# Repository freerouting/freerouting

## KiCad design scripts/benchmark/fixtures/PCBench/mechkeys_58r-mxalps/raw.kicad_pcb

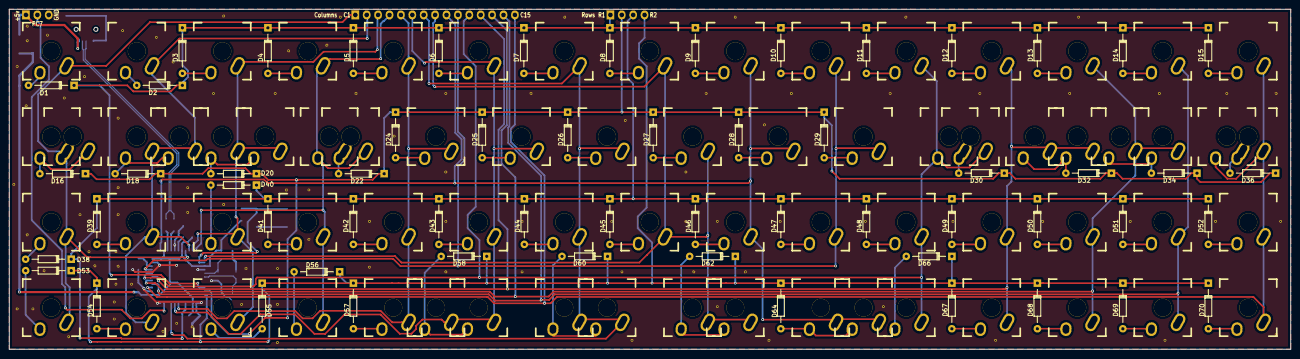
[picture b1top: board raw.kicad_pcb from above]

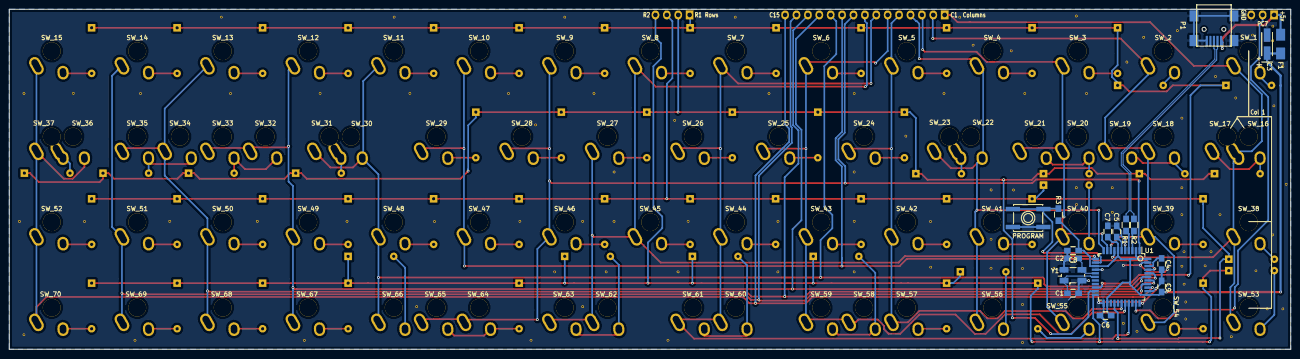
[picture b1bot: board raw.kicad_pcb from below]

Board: 2 copper layers, 285.5 x 75.8 mm, 148 parts (17 on the bottom side), 90 nets.

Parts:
C1, C2, C4, C6, C7, C8, C9: C_Small; C_0805_HandSoldering
C3: CP_Small; TantalC_SizeA_EIA-3216_HandSoldering
C5: 1µF; C_0805_HandSoldering
D1, D2, D3, D4, D5, D6, D7, D8, D9, D10, D11, D12, D13, D14, D15, D16, D18, D20, D22, D24, D25, D26, D27, D28, D29, D30, D32, D34, D36, D38, D39, D40, D41, D42, D43, D44, D45, D46, D47, D48, D49, D50, D51, D52, D53, D54, D55, D56, D57, D58, D60, D62, D64, D66, D67, D68, D69, D70: D; Diode_DO-35_SOD27_Horizontal_RM10
F1: F_Small; Fuse_SMD1206_HandSoldering
P1: USB_OTG; USB_Mini-B
P2: CONN_01X03; Socket_Strip_Straight_1x03_NoOverlay
P3: CONN_01X15; Socket_Strip_Straight_1x15_NoOverlay
P4: CONN_01X04; Socket_Strip_Straight_1x04_NoOverlay
PROGRAM: SW_PUSH; SW_SPST_EVQP0
R1, R2: 22; R_0805_HandSoldering
R3: 10k; R_0805_HandSoldering
SW_1, SW_2, SW_3, SW_4, SW_5, SW_6, SW_7, SW_8, SW_9, SW_10, SW_11, SW_12, SW_13, SW_14, SW_15, SW_16, SW_17, SW_18, SW_19, SW_20, SW_21, SW_22, SW_23, SW_24, SW_25, SW_26, SW_27, SW_28, SW_29, SW_30, SW_31, SW_32, SW_33, SW_34, SW_35, SW_36, SW_37, SW_38, SW_39, SW_40, SW_41, SW_42, SW_43, SW_44, SW_45, SW_46, SW_47, SW_48, SW_49, SW_50, SW_51, SW_52, SW_53, SW_54, SW_55, SW_56, SW_57, SW_58, SW_59, SW_60, SW_61, SW_62, SW_63, SW_64, SW_65, SW_66, SW_67, SW_68, SW_69, SW_70: MX_LED; MXALPS-NOLED
U1: ATmega32U4; LQFP-44_10x10mm_Pitch0.8mm
Y1: Crystal_Small; Crystal_SMD_5032_4Pads

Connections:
+5V: C3.1, C6.1, C7.1, C8.1, C9.1, F1.2, R3.2, U1.2, U1.7, U1.14, U1.24, U1.34, U1.44
C1: P3.1, SW_1.SW1, SW_16.SW1, SW_17.SW2, SW_38.SW1, SW_53.SW1, U1.8
C2: P3.2, SW_2.SW1, SW_18.SW1, SW_19.SW1, SW_39.SW1, SW_54.SW1, U1.9
C3: P3.3, SW_3.SW1, SW_20.SW1, SW_21.SW1, SW_40.SW1, SW_55.SW1, U1.10
C4: P3.4, SW_4.SW1, SW_22.SW2, SW_23.SW1, SW_41.SW1, SW_56.SW1, U1.11
C5: P3.5, SW_5.SW1, SW_24.SW1, SW_42.SW1, SW_57.SW1, U1.28
C6: P3.6, SW_6.SW1, SW_25.SW1, SW_43.SW1, SW_58.SW1, SW_59.SW1, U1.29
C7: P3.7, SW_7.SW1, SW_26.SW1, SW_44.SW1, SW_60.SW1, SW_61.SW1, U1.30
C8: P3.8, SW_8.SW1, SW_27.SW1, SW_45.SW1, SW_62.SW1, SW_63.SW1, U1.12
C9: P3.9, SW_9.SW1, SW_28.SW1, SW_46.SW1, SW_64.SW1, SW_65.SW1, U1.1
C10: P3.10, SW_10.SW1, SW_29.SW1, SW_47.SW1, U1.41
C11: P3.11, SW_11.SW1, SW_30.SW2, SW_31.SW1, SW_48.SW1, SW_66.SW1, U1.40
C12: P3.12, SW_12.SW1, SW_32.SW1, SW_33.SW1, SW_49.SW1, SW_67.SW1, U1.39
C13: P3.13, SW_13.SW1, SW_34.SW1, SW_35.SW1, SW_50.SW1, SW_68.SW1, U1.38
C14: P3.14, SW_14.SW1, SW_51.SW1, SW_69.SW1, U1.37
C15: P3.15, SW_15.SW1, SW_36.SW2, SW_37.SW1, SW_52.SW1, SW_70.SW1, U1.36
D+: R1.1, U1.4
D-: R2.1, U1.3
GND: C1.1, C2.2, C3.2, C4.2, C5.2, C6.2, C7.2, C8.2, C9.2, P1.5, P1.6, P2.3, PROGRAM.1, U1.5, U1.15, U1.23, U1.33, U1.35, U1.43, Y1.3
unnamed: C1.2, U1.17, Y1.1
unnamed: C2.1, U1.16, Y1.2
unnamed: C4.1, U1.42
unnamed: C5.1, U1.6
unnamed: D1.2, SW_1.SW2
unnamed: D2.2, SW_2.SW2
unnamed: D3.2, SW_3.SW2
unnamed: D4.2, SW_4.SW2
unnamed: D5.2, SW_5.SW2
unnamed: D6.2, SW_6.SW2
unnamed: D7.2, SW_7.SW2
unnamed: D8.2, SW_8.SW2
unnamed: D9.2, SW_9.SW2
unnamed: D10.2, SW_10.SW2
unnamed: D11.2, SW_11.SW2
unnamed: D12.2, SW_12.SW2
unnamed: D13.2, SW_13.SW2
unnamed: D14.2, SW_14.SW2
unnamed: D15.2, SW_15.SW2
unnamed: D16.2, SW_16.SW2, SW_17.SW1
unnamed: D18.2, SW_18.SW2, SW_19.SW2
unnamed: D20.2, SW_20.SW2, SW_21.SW2
unnamed: D22.2, SW_22.SW1, SW_23.SW2
unnamed: D24.2, SW_24.SW2
unnamed: D25.2, SW_25.SW2
unnamed: D26.2, SW_26.SW2
unnamed: D27.2, SW_27.SW2
unnamed: D28.2, SW_28.SW2
unnamed: D29.2, SW_29.SW2
unnamed: D30.2, SW_30.SW1, SW_31.SW2
unnamed: D32.2, SW_32.SW2, SW_33.SW2
unnamed: D34.2, SW_34.SW2, SW_35.SW2
unnamed: D36.2, SW_36.SW1, SW_37.SW2
unnamed: D38.2, SW_38.SW2
unnamed: D39.2, SW_39.SW2
unnamed: D40.2, SW_40.SW2
unnamed: D41.2, SW_41.SW2
unnamed: D42.2, SW_42.SW2
unnamed: D43.2, SW_43.SW2
unnamed: D44.2, SW_44.SW2
unnamed: D45.2, SW_45.SW2
unnamed: D46.2, SW_46.SW2
unnamed: D47.2, SW_47.SW2
unnamed: D48.2, SW_48.SW2
unnamed: D49.2, SW_49.SW2
unnamed: D50.2, SW_50.SW2
unnamed: D51.2, SW_51.SW2
unnamed: D52.2, SW_52.SW2
unnamed: D53.2, SW_53.SW2
unnamed: D54.2, SW_54.SW2
unnamed: D55.2, SW_55.SW2
unnamed: D56.2, SW_56.SW2
unnamed: D57.2, SW_57.SW2
unnamed: D58.2, SW_58.SW2, SW_59.SW2
unnamed: D60.2, SW_60.SW2, SW_61.SW2
unnamed: D62.2, SW_62.SW2, SW_63.SW2
unnamed: D64.2, SW_64.SW2, SW_65.SW2
unnamed: D66.2, SW_66.SW2
unnamed: D67.2, SW_67.SW2
unnamed: D68.2, SW_68.SW2
unnamed: D69.2, SW_69.SW2
unnamed: D70.2, SW_70.SW2
unnamed: PROGRAM.2, R3.1, U1.13
PC7: P2.2, U1.32
R1: D1.1, D2.1, D3.1, D4.1, D5.1, D6.1, D7.1, D8.1, D9.1, D10.1, D11.1, D12.1, D13.1, D14.1, D15.1, P4.1, U1.20
R2: D16.1, D18.1, D20.1, D22.1, D24.1, D25.1, D26.1, D27.1, D28.1, D29.1, D30.1, D32.1, D34.1, D36.1, P4.2, U1.21
R3: D38.1, D39.1, D40.1, D41.1, D42.1, D43.1, D44.1, D45.1, D46.1, D47.1, D48.1, D49.1, D50.1, D51.1, D52.1, P4.3, U1.26
R4: D53.1, D54.1, D55.1, D56.1, D57.1, D58.1, D60.1, D62.1, D64.1, D66.1, D67.1, D68.1, D69.1, D70.1, P4.4, U1.22
USB+: P1.3, R1.2
USB-: P1.2, R2.2
VUSB: F1.1, P1.1, P2.1

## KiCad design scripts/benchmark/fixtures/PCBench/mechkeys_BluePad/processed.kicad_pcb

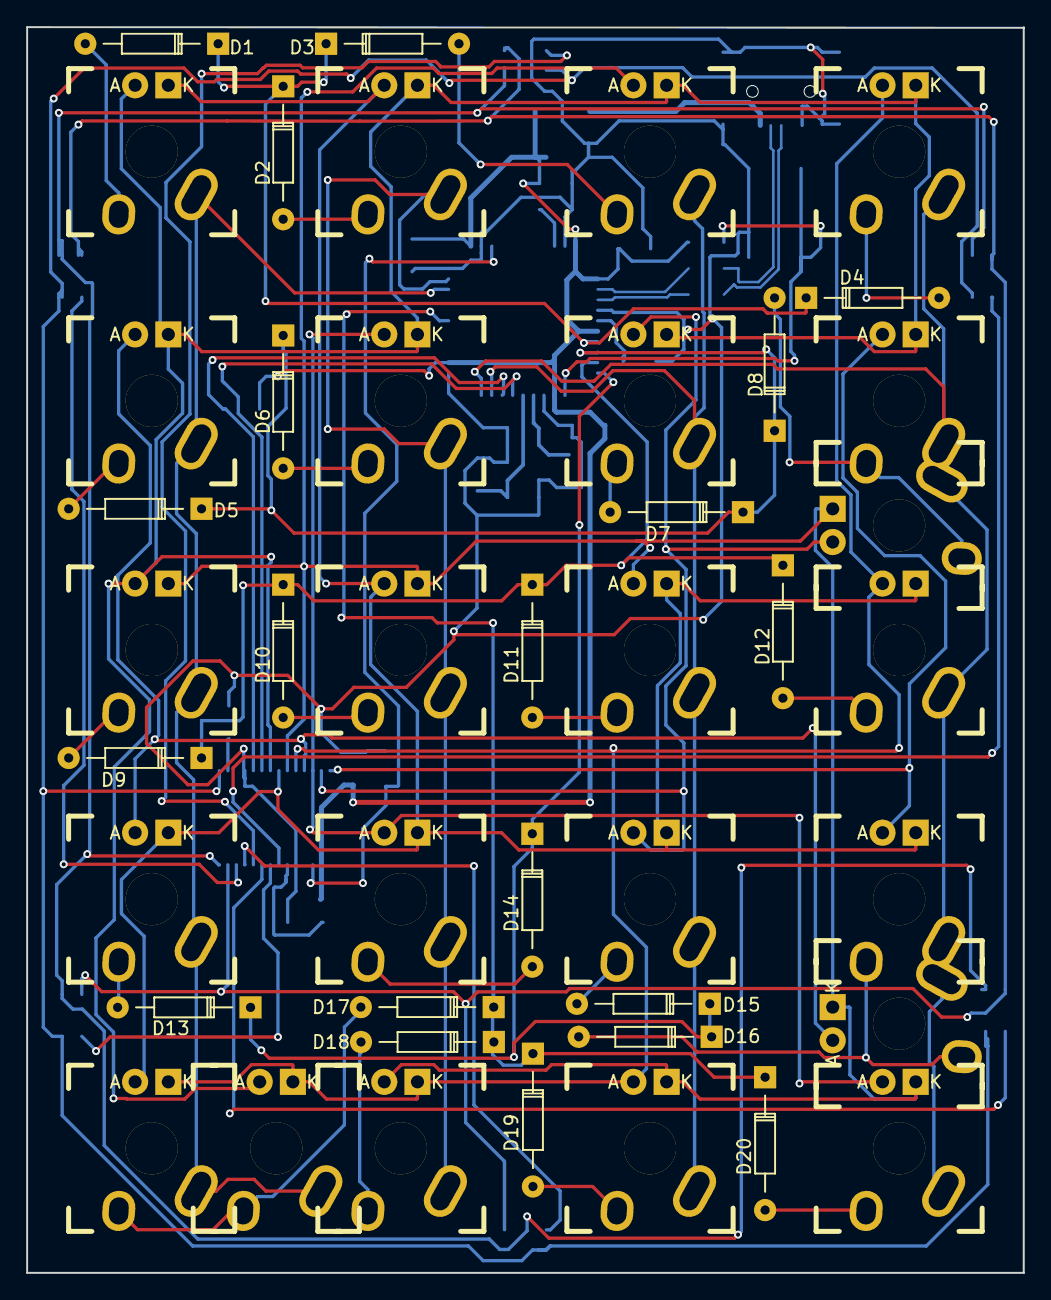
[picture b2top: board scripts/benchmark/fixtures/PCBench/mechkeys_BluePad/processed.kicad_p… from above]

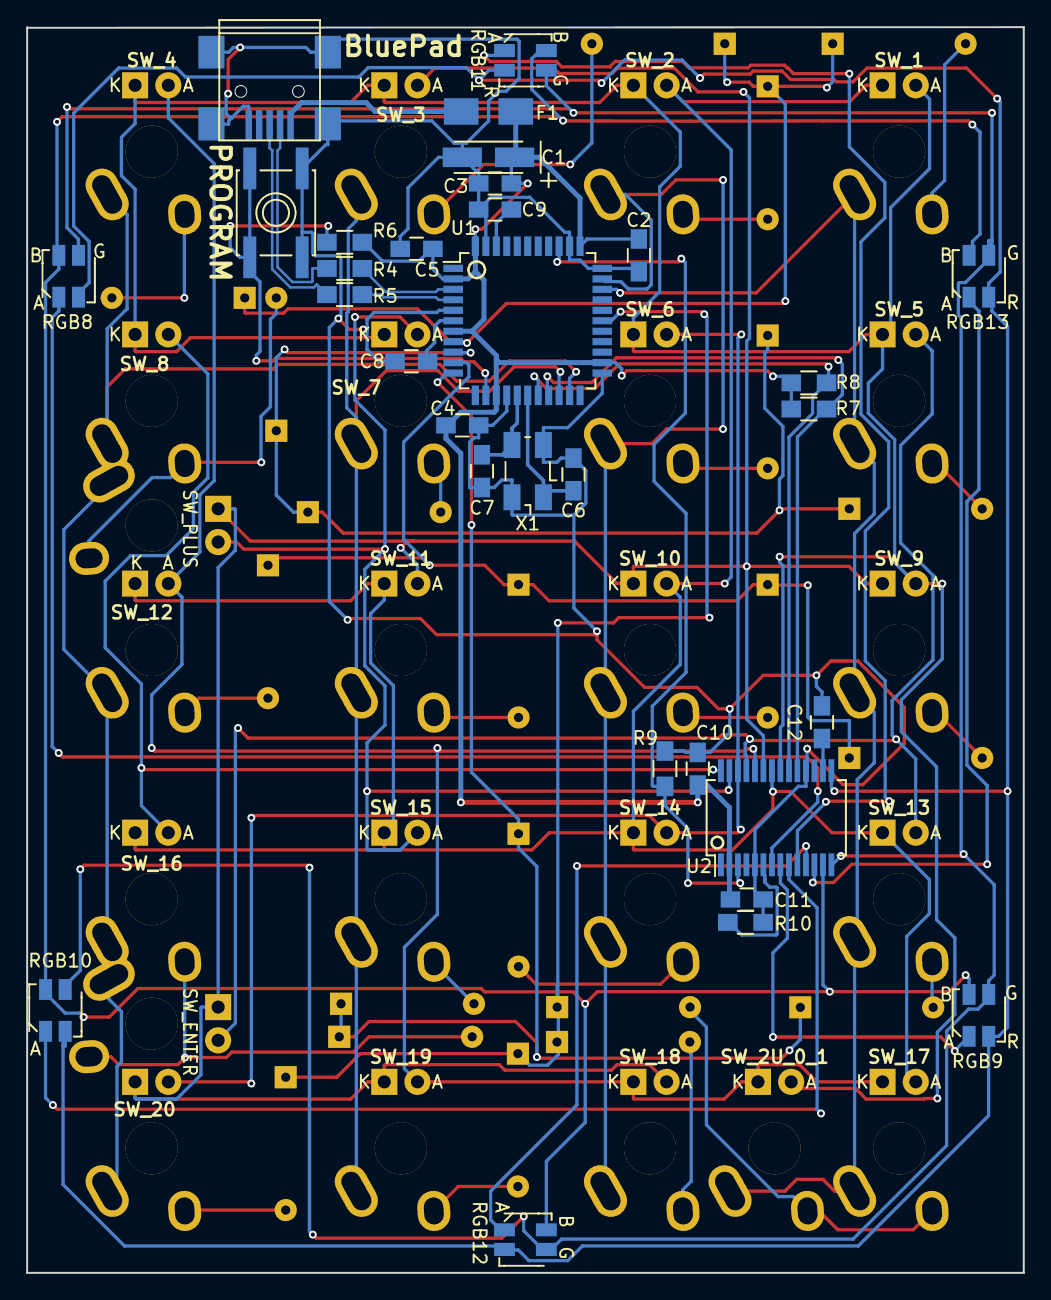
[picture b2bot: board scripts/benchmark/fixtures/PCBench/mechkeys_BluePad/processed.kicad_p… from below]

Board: 2 copper layers, 76.2 x 95.2 mm, 74 parts (31 on the bottom side), 63 nets.

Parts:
C1: 10µF; TantalC_SizeA_EIA-3216_HandSoldering
C2, C3, C4, C5, C9, C11, C12: 0.1µF; C_0805_HandSoldering
C6, C7: 18pF; C_0805_HandSoldering
C8, C10: 1µF; C_0805_HandSoldering
D1, D2, D3, D4, D5, D6, D7, D8, D9, D10, D11, D12, D13, D14, D15, D16, D17, D18, D19, D20: D; Diode_DO-35_SOD27_Horizontal_RM10
F1: FP_Small; Fuse_SMD1206_HandSoldering
J1: USB_OTG; USB_Mini-B
R4, R5: 22; R_0805_HandSoldering
R6: 10k; R_0805_HandSoldering
R7, R8: 4.7KΩ; R_0805_HandSoldering
R9: 100KΩ; R_0805_HandSoldering
R10: 20KΩ; R_0805_HandSoldering
RGB8, RGB9, RGB10, RGB11, RGB12, RGB13: Led_RGB_CA; SMP4-RGB
SW1: SW_RST; SW_SPST_EVQP0
SW_1, SW_2, SW_2U_0_1, SW_2U_PLUS_1, SW_3, SW_4, SW_5, SW_6, SW_7, SW_8, SW_9, SW_10, SW_11, SW_12, SW_13, SW_14, SW_15, SW_16, SW_17, SW_18, SW_19, SW_20: MX_LED; MXALPS
SW_2U_ENTER_1: MX_LED; MXALPS_LED_PANEL
U1: ATMEGA32U4RC-A; TQFP-44_10x10mm_Pitch0.8mm
U2: IS31FL3731; SSOP-28_5.3x10.2mm_Pitch0.65mm
X1: 16Mhz; Crystal_SMD_5032_4Pads

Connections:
+5V: C1.1, C2.1, C3.1, C4.1, C5.1, C10.1, C11.1, F1.2, R6.2, R7.1, R8.1, U1.2, U1.7, U1.14, U1.24, U1.34, U1.44, U2.2
C1: SW_1.SW1, SW_2U_0_1.SW1, SW_5.SW1, SW_9.SW1, SW_13.SW1, SW_17.SW1, U1.31
C2: SW_2.SW1, SW_6.SW1, SW_10.SW1, SW_14.SW1, SW_18.SW1, U1.32
C3: SW_3.SW1, SW_7.SW1, SW_11.SW1, SW_15.SW1, SW_19.SW1, U1.20
C4: SW_2U_ENTER_1.SW1, SW_2U_PLUS_1.SW1, SW_4.SW1, SW_8.SW1, SW_12.SW1, SW_16.SW1, SW_20.SW1, U1.21
CA1: SW_1.A, SW_2.K, SW_2U_0_1.A, SW_3.K, SW_4.K, SW_5.K, SW_6.K, SW_7.K, SW_8.K, SW_9.A, U2.21
CA2: SW_1.K, SW_2.A, SW_10.A, SW_11.K, SW_12.K, SW_13.K, SW_14.K, SW_15.K, SW_16.K, SW_17.A, U2.22
CA3: SW_2U_ENTER_1.K, SW_2U_PLUS_1.K, SW_3.A, SW_9.K, SW_10.K, SW_11.A, SW_18.A, SW_19.K, SW_20.K, U2.23
CA4: SW_2U_0_1.K, SW_4.A, SW_12.A, SW_17.K, SW_18.K, SW_19.A, U2.24
CA5: SW_2U_ENTER_1.A, SW_5.A, SW_13.A, U2.25
CA6: SW_6.A, SW_14.A, SW_20.A, U2.26
CA7: SW_2U_PLUS_1.A, SW_7.A, SW_15.A, U2.27
CA8: SW_8.A, SW_16.A, U2.28
CB1: RGB8.1, U2.7
CB2: RGB9.1, U2.8
CB3: RGB10.1, U2.9
CB4: RGB11.1, U2.10
CB5: RGB12.1, U2.11
CB6: RGB13.1, U2.12
CB7: RGB8.4, RGB9.4, RGB10.4, RGB11.4, RGB12.4, RGB13.4, U2.13
CB8: RGB8.3, RGB9.3, RGB10.3, RGB11.3, RGB12.3, RGB13.3, U2.14
CB9: RGB8.2, RGB9.2, RGB10.2, RGB11.2, RGB12.2, RGB13.2, U2.15
D+: R5.1, U1.4
D-: R4.1, U1.3
GND: C1.2, C2.2, C3.2, C4.2, C5.2, C6.2, C7.2, C8.2, C9.2, C10.2, C11.2, C12.2, J1.5, J1.6, R9.2, R10.2, SW1.1, U1.5, U1.15, U1.23, U1.33, U1.35, U1.43, U2.5, U2.18, X1.3
LED_NSRT: R9.1, U1.36, U2.3
LED_SCL: R8.2, U1.18, U2.20
LED_SDA: R7.2, U1.19, U2.19
unnamed: C6.1, U1.17, X1.1
unnamed: C7.1, U1.16, X1.2
unnamed: C8.1, U1.6
unnamed: C9.1, U1.42
unnamed: C12.1, U2.16
unnamed: D1.2, SW_1.SW2
unnamed: D2.2, SW_2.SW2
unnamed: D3.2, SW_3.SW2
unnamed: D4.2, SW_4.SW2
unnamed: D5.2, SW_5.SW2
unnamed: D6.2, SW_6.SW2
unnamed: D7.2, SW_7.SW2
unnamed: D8.2, SW_2U_PLUS_1.SW2, SW_8.SW2
unnamed: D9.2, SW_9.SW2
unnamed: D10.2, SW_10.SW2
unnamed: D11.2, SW_11.SW2
unnamed: D12.2, SW_12.SW2
unnamed: D13.2, SW_13.SW2
unnamed: D14.2, SW_14.SW2
unnamed: D15.2, SW_15.SW2
unnamed: D16.2, SW_2U_ENTER_1.SW2, SW_16.SW2
unnamed: D17.2, SW_2U_0_1.SW2, SW_17.SW2
unnamed: D18.2, SW_18.SW2
unnamed: D19.2, SW_19.SW2
unnamed: D20.2, SW_20.SW2
unnamed: F1.1, J1.1
unnamed: R10.1, U2.6
R1: D1.1, D2.1, D3.1, D4.1, U1.8
R2: D5.1, D6.1, D7.1, D8.1, U1.9
R3: D9.1, D10.1, D11.1, D12.1, U1.10
R4: D13.1, D14.1, D15.1, D16.1, U1.11
R5: D17.1, D18.1, D19.1, D20.1, U1.28
RST: R6.1, SW1.2, U1.13
USB+: J1.3, R5.2
USB-: J1.2, R4.2

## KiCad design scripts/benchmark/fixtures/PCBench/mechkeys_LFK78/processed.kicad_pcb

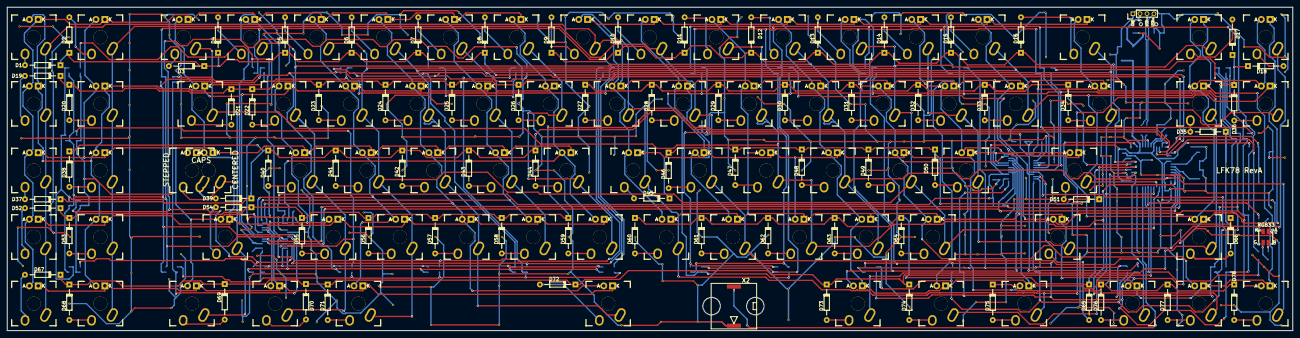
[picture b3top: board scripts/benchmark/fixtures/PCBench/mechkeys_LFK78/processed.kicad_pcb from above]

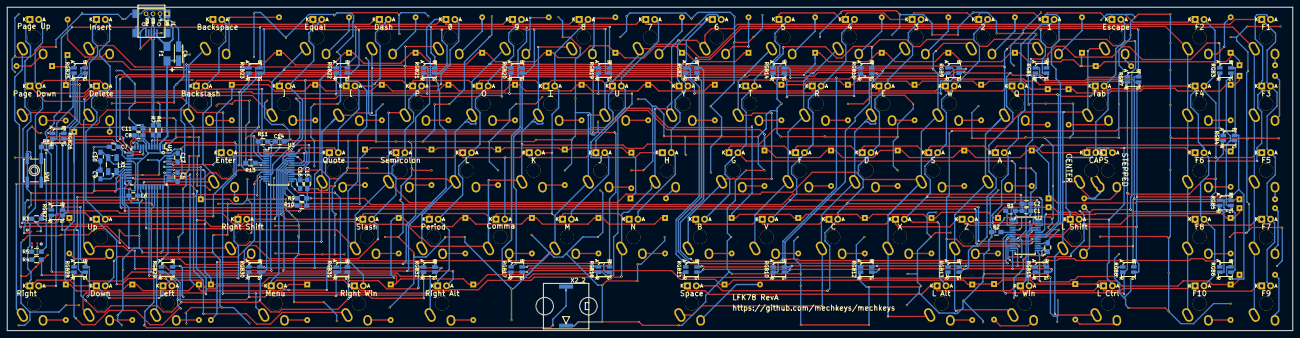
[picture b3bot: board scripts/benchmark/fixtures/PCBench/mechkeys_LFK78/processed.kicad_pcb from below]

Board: 2 copper layers, 367.8 x 92.5 mm, 226 parts (66 on the bottom side), 159 nets.

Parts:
C1, C11, C14: 1µF; C_0805_HandSoldering
C2, C3, C5, C6, C7, C8, C12, C15, C16: 0.1µF; C_0805_HandSoldering
C4: 10µF; TantalC_SizeA_EIA-3216_HandSoldering
C9, C10: 18pF; C_0805_HandSoldering
CHERRY: MX; CHERRY_PCB_625H_STABILIZER
D1, D2, D3, D4, D5, D6, D7, D8, D9, D10, D11, D12, D13, D14, D15, D16, D17, D18, D19, D20, D21, D22, D23, D24, D25, D26, D27, D28, D29, D30, D31, D32, D33, D34, D35, D36, D37, D38, D39, D40, D41, D42, D43, D44, D45, D46, D47, D48, D49, D50, D51, D52, D53, D54, D55, D56, D57, D58, D59, D60, D61, D62, D63, D64, D65, D66, D67, D68, D69, D70, D71, D72, D73, D74, D75, D76, D77, D78: D; Diode_DO-35_SOD27_Horizontal_RM10
F1: FP_Small; Fuse_SMD1206_HandSoldering
J1: USB_OTG; USB_Mini-B
R1, R11: 10KΩ; R_0805_HandSoldering
R2, R13: 20KΩ; R_0805_HandSoldering
R3: 150Ω; R_0805_HandSoldering
R4, R5: 120Ω; R_0805_HandSoldering
R6, R7: 22; R_0805_HandSoldering
R8: 10k; R_0805_HandSoldering
R9, R10: 4.7KΩ; R_0805_HandSoldering
RGB1, RGB2, RGB3, RGB4, RGB5, RGB6, RGB7, RGB8, RGB9, RGB10, RGB11, RGB12, RGB13, RGB14, RGB15, RGB16, RGB17, RGB18, RGB19, RGB20, RGB21, RGB22, RGB23, RGB25, RGB26, RGB27, RGB28, RGB29, RGB30, RGB31, RGB32: Led_RGB_CA; SMP4-RGB
RGB33: Led_RGB_CA; SMP4-RGB-PIPE
SW1: SW_RST; SW_SPST_EVQP0
SW_A_40: MX_LED; MXALPS_LED_PANEL
SW_Alt_71, SW_Alt_73: MX_LED; MXALPS_LED_PANEL
SW_B_59: MX_LED; MXALPS_LED_PANEL
SW_Backspace_16: MX_LED; MXALPS_LED_PANEL
SW_C_57: MX_LED; MXALPS_LED_PANEL
SW_CapStep_39: MX_LED; MXALPS_LED_PANEL
SW_Caps_39: MX_LED; MXALPS_LED_PANEL
SW_Ctrl_69: MX_LED; MXALPS_LED_PANEL
SW_D_42: MX_LED; MXALPS_LED_PANEL
SW_Del_35: MX_LED; MXALPS_LED_PANEL
SW_E_24: MX_LED; MXALPS_LED_PANEL
SW_Enter_51: MX_LED; MXALPS_LED_PANEL
SW_F1_1, SW_F2_2, SW_F3_19, SW_F4_20, SW_F5_37, SW_F6_38, SW_F7_52, SW_F8_53, SW_F9_67, SW_F10_68: MX_LED; MXALPS_LED_PANEL
SW_F_43: MX_LED; MXALPS_LED_PANEL
SW_G_44: MX_LED; MXALPS_LED_PANEL
SW_H_45: MX_LED; MXALPS_LED_PANEL
SW_I_29: MX_LED; MXALPS_LED_PANEL
SW_Ins_17: MX_LED; MXALPS_LED_PANEL
SW_J_46: MX_LED; MXALPS_LED_PANEL
SW_K_47: MX_LED; MXALPS_LED_PANEL
SW_L_48: MX_LED; MXALPS_LED_PANEL
SW_M_61: MX_LED; MXALPS_LED_PANEL
SW_Menu_75: MX_LED; MXALPS_LED_PANEL
SW_N_60: MX_LED; MXALPS_LED_PANEL
SW_O_30: MX_LED; MXALPS_LED_PANEL
SW_P_31: MX_LED; MXALPS_LED_PANEL
SW_PgDn_36: MX_LED; MXALPS_LED_PANEL
SW_PgUp_18: MX_LED; MXALPS_LED_PANEL
SW_Q_22: MX_LED; MXALPS_LED_PANEL
SW_R_25: MX_LED; MXALPS_LED_PANEL
SW_S_41: MX_LED; MXALPS_LED_PANEL
SW_Shift_54, SW_Shift_65: MX_LED; MXALPS_LED_PANEL
SW_T_26: MX_LED; MXALPS_LED_PANEL
SW_Tab_21: MX_LED; MXALPS_LED_PANEL
SW_U_28: MX_LED; MXALPS_LED_PANEL
SW_V_58: MX_LED; MXALPS_LED_PANEL
SW_W_23: MX_LED; MXALPS_LED_PANEL
SW_Win_70, SW_Win_74: MX_LED; MXALPS_LED_PANEL
SW_X4Y1_3, SW_X5Y1_4, SW_X6Y1_5, SW_X7Y1_6, SW_X8Y1_7, SW_X8Y5_72, SW_X9Y1_8, SW_X10Y1_9, SW_X11Y1_10, SW_X12Y1_11, SW_X13Y1_12, SW_X13Y4_62, SW_X14Y1_13, SW_X14Y4_63, SW_X15Y1_14, SW_X15Y2_32, SW_X15Y3_49, SW_X15Y4_64, SW_X16Y1_15, SW_X16Y2_33, SW_X16Y3_50, SW_X17Y2_34, SW_X18Y5_76, SW_X19Y4_66, SW_X19Y5_77, SW_X20Y5_78: MX_LED; MXALPS_LED_PANEL
SW_X_56: MX_LED; MXALPS_LED_PANEL
SW_Y_27: MX_LED; MXALPS_LED_PANEL
SW_Z_55: MX_LED; MXALPS_LED_PANEL
U1: ATMEGA32U4RC-A; TQFP-44_10x10mm_Pitch0.8mm
U2, U3: IS31FL3731; SSOP-28_5.3x10.2mm_Pitch0.65mm
X1: 16Mhz; Crystal_SMD_5032_4Pads
X2, X2_2: PiezoelectricCrystal-TwoElectrodes_EN60617_04-07-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; piezo-12x12

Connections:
+5V: C1.1, C2.1, C4.1, C5.1, C6.1, C7.1, C8.1, C14.1, C15.1, F1.2, R1.2, R8.2, R9.1, R10.1, R11.2, RGB33.1, U1.2, U1.7, U1.14, U1.24, U1.34, U1.44, U2.2, U3.2, U3.18
AUDIO: U1.31, X2.2, X2_2.2
C1: SW_F1_1.SW1, SW_F3_19.SW1, SW_F5_37.SW1, SW_F7_52.SW1, SW_F9_67.SW1, SW_H_45.SW1, SW_Menu_75.SW1, SW_N_60.SW1, SW_X10Y1_9.SW1, SW_Y_27.SW1, U1.1
C2: SW_F2_2.SW1, SW_F4_20.SW1, SW_F6_38.SW1, SW_F8_53.SW1, SW_F10_68.SW1, SW_J_46.SW1, SW_M_61.SW1, SW_U_28.SW1, SW_X11Y1_10.SW1, SW_X18Y5_76.SW1, U1.36
C3: SW_CapStep_39.SW2, SW_Caps_39.SW1, SW_Ctrl_69.SW1, SW_I_29.SW1, SW_K_47.SW1, SW_Shift_54.SW1, SW_Tab_21.SW1, SW_X4Y1_3.SW1, SW_X12Y1_11.SW1, SW_X13Y4_62.SW1, SW_X19Y5_77.SW1, U1.20
C4: SW_A_40.SW1, SW_L_48.SW1, SW_O_30.SW1, SW_Q_22.SW1, SW_Win_70.SW1, SW_X5Y1_4.SW1, SW_X13Y1_12.SW1, SW_X14Y4_63.SW1, SW_X20Y5_78.SW1, SW_Z_55.SW1, U1.21
C5: SW_Alt_71.SW1, SW_Ins_17.SW1, SW_P_31.SW1, SW_S_41.SW1, SW_W_23.SW1, SW_X6Y1_5.SW1, SW_X14Y1_13.SW1, SW_X15Y3_49.SW1, SW_X15Y4_64.SW1, SW_X_56.SW1, U1.25
C6: SW_C_57.SW1, SW_D_42.SW1, SW_E_24.SW1, SW_PgUp_18.SW1, SW_Shift_65.SW1, SW_X7Y1_6.SW1, SW_X8Y5_72.SW1, SW_X15Y1_14.SW1, SW_X15Y2_32.SW1, SW_X16Y3_50.SW1, U1.22
C7: SW_Alt_73.SW1, SW_Del_35.SW1, SW_Enter_51.SW1, SW_F_43.SW1, SW_R_25.SW1, SW_V_58.SW1, SW_X8Y1_7.SW1, SW_X16Y1_15.SW1, SW_X16Y2_33.SW1, SW_X19Y4_66.SW1, U1.26
C8: SW_B_59.SW1, SW_Backspace_16.SW1, SW_G_44.SW1, SW_PgDn_36.SW1, SW_T_26.SW1, SW_Win_74.SW1, SW_X9Y1_8.SW1, SW_X17Y2_34.SW1, U1.27
D+: R7.1, U1.4
D-: R6.1, U1.3
GND: C1.2, C2.2, C3.2, C4.2, C5.2, C6.2, C7.2, C8.2, C9.2, C10.2, C11.2, C12.2, C14.2, C15.2, C16.2, J1.5, J1.6, R2.2, R13.2, SW1.1, U1.5, U1.15, U1.23, U1.33, U1.35, U1.43, U2.5, U2.18, U3.5, X2.1, X2_2.1
LED_SCL: R10.2, U1.18, U2.20, U3.20
LED_SDA: R9.2, U1.19, U2.19, U3.19
L_CA1: SW_F1_1.K, SW_F2_2.K, SW_F3_19.A, SW_F5_37.A, SW_F7_52.A, SW_F9_67.A, SW_X4Y1_3.K, SW_X5Y1_4.K, SW_X6Y1_5.K, SW_X7Y1_6.K, SW_X8Y1_7.K, SW_X9Y1_8.K, U2.21
L_CA2: SW_E_24.K, SW_F1_1.A, SW_F3_19.K, SW_F4_20.K, SW_F6_38.A, SW_F8_53.A, SW_F10_68.A, SW_Q_22.K, SW_R_25.K, SW_T_26.K, SW_Tab_21.K, SW_W_23.K, U2.22
L_CA3: SW_A_40.K, SW_CapStep_39.K, SW_Caps_39.K, SW_Ctrl_69.A, SW_D_42.K, SW_F2_2.A, SW_F4_20.A, SW_F5_37.K, SW_F6_38.K, SW_F_43.K, SW_G_44.K, SW_S_41.K, SW_Shift_54.A, U2.23
L_CA4: SW_B_59.K, SW_C_57.K, SW_CapStep_39.A, SW_Caps_39.A, SW_F7_52.K, SW_F8_53.K, SW_Shift_54.K, SW_Tab_21.A, SW_V_58.K, SW_Win_70.A, SW_X4Y1_3.A, SW_X_56.K, SW_Z_55.K, U2.24
L_CA5: SW_A_40.A, SW_Alt_71.K, SW_Ctrl_69.K, SW_F9_67.K, SW_F10_68.K, SW_Q_22.A, SW_Win_70.K, SW_X5Y1_4.A, SW_X8Y5_72.K, SW_Z_55.A, U2.25
L_CA6: SW_Alt_71.A, SW_S_41.A, SW_W_23.A, SW_X6Y1_5.A, SW_X_56.A, U2.26
L_CA7: SW_C_57.A, SW_D_42.A, SW_E_24.A, SW_X7Y1_6.A, SW_X8Y5_72.A, U2.27
L_CA8: SW_F_43.A, SW_R_25.A, SW_V_58.A, SW_X8Y1_7.A, U2.28
L_CA9: SW_B_59.A, SW_G_44.A, SW_T_26.A, SW_X9Y1_8.A, U2.1
L_CB1: RGB1.2, RGB2.2, RGB3.2, RGB4.2, RGB5.2, RGB6.2, RGB7.2, RGB8.2, RGB9.1, U2.7
L_CB2: RGB1.1, RGB2.3, RGB3.3, RGB4.3, RGB5.3, RGB6.3, RGB7.3, RGB8.3, RGB10.1, U2.8
L_CB3: RGB1.3, RGB2.1, RGB3.4, RGB4.4, RGB5.4, RGB6.4, RGB7.4, RGB8.4, RGB11.1, U2.9
L_CB4: RGB1.4, RGB2.4, RGB3.1, RGB12.1, U2.10
L_CB5: RGB4.1, RGB13.1, U2.11
L_CB6: RGB5.1, RGB14.1, RGB15.4, RGB16.4, U2.12
L_CB7: RGB6.1, RGB9.4, RGB10.4, RGB11.4, RGB12.4, RGB13.4, RGB14.4, RGB15.1, RGB16.3, U2.13
L_CB8: RGB7.1, RGB9.3, RGB10.3, RGB11.3, RGB12.3, RGB13.3, RGB14.3, RGB15.3, RGB16.1, U2.14
L_CB9: RGB8.1, RGB9.2, RGB10.2, RGB11.2, RGB12.2, RGB13.2, RGB14.2, RGB15.2, RGB16.2, U2.15
unnamed: C3.1, U2.16
unnamed: C9.1, U1.17, X1.1
unnamed: C10.1, U1.16, X1.2
unnamed: C11.1, U1.6
unnamed: C12.1, U1.42
unnamed: C16.1, U3.16
unnamed: D1.2, SW_F1_1.SW2
unnamed: D2.2, SW_F2_2.SW2
unnamed: D3.2, SW_X4Y1_3.SW2
unnamed: D4.2, SW_X5Y1_4.SW2
unnamed: D5.2, SW_X6Y1_5.SW2
unnamed: D6.2, SW_X7Y1_6.SW2
unnamed: D7.2, SW_X8Y1_7.SW2
unnamed: D8.2, SW_X9Y1_8.SW2
unnamed: D9.2, SW_X10Y1_9.SW2
unnamed: D10.2, SW_X11Y1_10.SW2
unnamed: D11.2, SW_X12Y1_11.SW2
unnamed: D12.2, SW_X13Y1_12.SW2
unnamed: D13.2, SW_X14Y1_13.SW2
unnamed: D14.2, SW_X15Y1_14.SW2
unnamed: D15.2, SW_X16Y1_15.SW2
unnamed: D16.2, SW_Backspace_16.SW2
unnamed: D17.2, SW_Ins_17.SW2
unnamed: D18.2, SW_PgUp_18.SW2
unnamed: D19.2, SW_F3_19.SW2
unnamed: D20.2, SW_F4_20.SW2
unnamed: D21.2, SW_Tab_21.SW2
unnamed: D22.2, SW_Q_22.SW2
unnamed: D23.2, SW_W_23.SW2
unnamed: D24.2, SW_E_24.SW2
unnamed: D25.2, SW_R_25.SW2
unnamed: D26.2, SW_T_26.SW2
unnamed: D27.2, SW_Y_27.SW2
unnamed: D28.2, SW_U_28.SW2
unnamed: D29.2, SW_I_29.SW2
unnamed: D30.2, SW_O_30.SW2
unnamed: D31.2, SW_P_31.SW2
unnamed: D32.2, SW_X15Y2_32.SW2
unnamed: D33.2, SW_X16Y2_33.SW2
unnamed: D34.2, SW_X17Y2_34.SW2
unnamed: D35.2, SW_Del_35.SW2
unnamed: D36.2, SW_PgDn_36.SW2
unnamed: D37.2, SW_F5_37.SW2
unnamed: D38.2, SW_F6_38.SW2
unnamed: D39.2, SW_CapStep_39.SW1, SW_Caps_39.SW2
unnamed: D40.2, SW_A_40.SW2
unnamed: D41.2, SW_S_41.SW2
unnamed: D42.2, SW_D_42.SW2
unnamed: D43.2, SW_F_43.SW2
unnamed: D44.2, SW_G_44.SW2
unnamed: D45.2, SW_H_45.SW2
unnamed: D46.2, SW_J_46.SW2
unnamed: D47.2, SW_K_47.SW2
unnamed: D48.2, SW_L_48.SW2
unnamed: D49.2, SW_X15Y3_49.SW2
unnamed: D50.2, SW_X16Y3_50.SW2
unnamed: D51.2, SW_Enter_51.SW2
unnamed: D52.2, SW_F7_52.SW2
unnamed: D53.2, SW_F8_53.SW2
unnamed: D54.2, SW_Shift_54.SW2
unnamed: D55.2, SW_Z_55.SW2
unnamed: D56.2, SW_X_56.SW2
unnamed: D57.2, SW_C_57.SW2
unnamed: D58.2, SW_V_58.SW2
unnamed: D59.2, SW_B_59.SW2
unnamed: D60.2, SW_N_60.SW2
unnamed: D61.2, SW_M_61.SW2
unnamed: D62.2, SW_X13Y4_62.SW2
unnamed: D63.2, SW_X14Y4_63.SW2
unnamed: D64.2, SW_X15Y4_64.SW2
unnamed: D65.2, SW_Shift_65.SW2
unnamed: D66.2, SW_X19Y4_66.SW2
unnamed: D67.2, SW_F9_67.SW2
unnamed: D68.2, SW_F10_68.SW2
unnamed: D69.2, SW_Ctrl_69.SW2
unnamed: D70.2, SW_Win_70.SW2
unnamed: D71.2, SW_Alt_71.SW2
unnamed: D72.2, SW_X8Y5_72.SW2
unnamed: D73.2, SW_Alt_73.SW2
unnamed: D74.2, SW_Win_74.SW2
unnamed: D75.2, SW_Menu_75.SW2
unnamed: D76.2, SW_X18Y5_76.SW2
unnamed: D77.2, SW_X19Y5_77.SW2
unnamed: D78.2, SW_X20Y5_78.SW2
unnamed: F1.1, J1.1
unnamed: R1.1, U2.3
unnamed: R2.1, U2.6
unnamed: R3.1, RGB33.2
unnamed: R4.1, RGB33.3
unnamed: R5.1, RGB33.4
unnamed: R11.1, U3.3
unnamed: R13.1, U3.6
PWM_BLUE: R5.2, U1.12
PWM_GREEN: R4.2, U1.30
PWM_RED: R3.2, U1.29
R1: D1.1, D2.1, D3.1, D4.1, D5.1, D6.1, D7.1, D8.1, U1.8
R2/SCK: D19.1, D20.1, D21.1, D22.1, D23.1, D24.1, D25.1, D26.1, U1.9
R3/MOSI: D37.1, D38.1, D39.1, D40.1, D41.1, D42.1, D43.1, D44.1, U1.10
R4/MISO: D52.1, D53.1, D54.1, D55.1, D56.1, D57.1, D58.1, D59.1, U1.11
R5: D67.1, D68.1, D69.1, D70.1, D71.1, D72.1, D73.1, D74.1, U1.28
R6: D9.1, D10.1, D11.1, D12.1, D13.1, D14.1, D15.1, D16.1, U1.41
R7: D27.1, D28.1, D29.1, D30.1, D31.1, D32.1, D33.1, D34.1, U1.40
R8: D45.1, D46.1, D47.1, D48.1, D49.1, D50.1, D51.1, U1.39
R9: D60.1, D61.1, D62.1, D63.1, D64.1, D65.1, D66.1, U1.38
R10: D17.1, D18.1, D35.1, D36.1, D75.1, D76.1, D77.1, D78.1, U1.37
RST: R8.1, SW1.2, U1.13
R_CA1: SW_Alt_73.A, SW_Backspace_16.K, SW_H_45.A, SW_N_60.A, SW_X10Y1_9.K, SW_X11Y1_10.K, SW_X12Y1_11.K, SW_X13Y1_12.K, SW_X14Y1_13.K, SW_X15Y1_14.K, SW_X16Y1_15.K, SW_Y_27.A, U3.21
R_CA2: SW_I_29.K, SW_J_46.A, SW_M_61.A, SW_O_30.K, SW_P_31.K, SW_U_28.K, SW_Win_74.A, SW_X10Y1_9.A, SW_X15Y2_32.K, SW_X16Y2_33.K, SW_X17Y2_34.K, SW_Y_27.K, U3.22
R_CA3: SW_Enter_51.K, SW_H_45.K, SW_J_46.K, SW_K_47.K, SW_L_48.K, SW_Menu_75.A, SW_PgDn_36.K, SW_U_28.A, SW_X11Y1_10.A, SW_X13Y4_62.A, SW_X15Y3_49.K, SW_X16Y3_50.K, U3.23
R_CA4: SW_I_29.A, SW_K_47.A, SW_M_61.K, SW_N_60.K, SW_PgUp_18.K, SW_Shift_65.K, SW_X12Y1_11.A, SW_X13Y4_62.K, SW_X14Y4_63.K, SW_X15Y4_64.K, SW_X18Y5_76.A, SW_X19Y4_66.K, U3.24
R_CA5: SW_Alt_73.K, SW_Del_35.K, SW_Ins_17.K, SW_L_48.A, SW_Menu_75.K, SW_O_30.A, SW_Win_74.K, SW_X13Y1_12.A, SW_X14Y4_63.A, SW_X18Y5_76.K, SW_X19Y5_77.K, SW_X20Y5_78.K, U3.25
R_CA6: SW_P_31.A, SW_X14Y1_13.A, SW_X15Y3_49.A, SW_X15Y4_64.A, SW_X19Y5_77.A, U3.26
R_CA7: SW_Shift_65.A, SW_X15Y1_14.A, SW_X15Y2_32.A, SW_X16Y3_50.A, SW_X20Y5_78.A, U3.27
R_CA8: SW_Enter_51.A, SW_Ins_17.A, SW_X16Y1_15.A, SW_X16Y2_33.A, SW_X19Y4_66.A, U3.28
R_CA9: SW_Backspace_16.A, SW_Del_35.A, SW_PgDn_36.A, SW_PgUp_18.A, SW_X17Y2_34.A, U3.1
R_CB1: RGB17.2, RGB18.2, RGB19.2, RGB20.2, RGB21.2, RGB22.2, RGB23.2, RGB25.1, U3.7
R_CB2: RGB17.1, RGB18.3, RGB19.3, RGB20.3, RGB21.3, RGB22.3, RGB23.3, RGB26.1, U3.8
R_CB3: RGB17.3, RGB18.1, RGB19.4, RGB20.4, RGB21.4, RGB22.4, RGB23.4, RGB27.1, U3.9
R_CB4: RGB17.4, RGB18.4, RGB19.1, RGB28.1, U3.10
R_CB5: RGB20.1, RGB29.1, U3.11
R_CB6: RGB21.1, RGB30.1, RGB31.4, RGB32.4, U3.12
R_CB7: RGB22.1, RGB25.4, RGB26.4, RGB27.4, RGB28.4, RGB29.4, RGB30.4, RGB31.1, RGB32.3, U3.13
R_CB8: RGB23.1, RGB25.3, RGB26.3, RGB27.3, RGB28.3, RGB29.3, RGB30.3, RGB31.3, RGB32.1, U3.14
R_CB9: RGB25.2, RGB26.2, RGB27.2, RGB28.2, RGB29.2, RGB30.2, RGB31.2, RGB32.2, U3.15
USB+: J1.3, R7.2
USB-: J1.2, R6.2
